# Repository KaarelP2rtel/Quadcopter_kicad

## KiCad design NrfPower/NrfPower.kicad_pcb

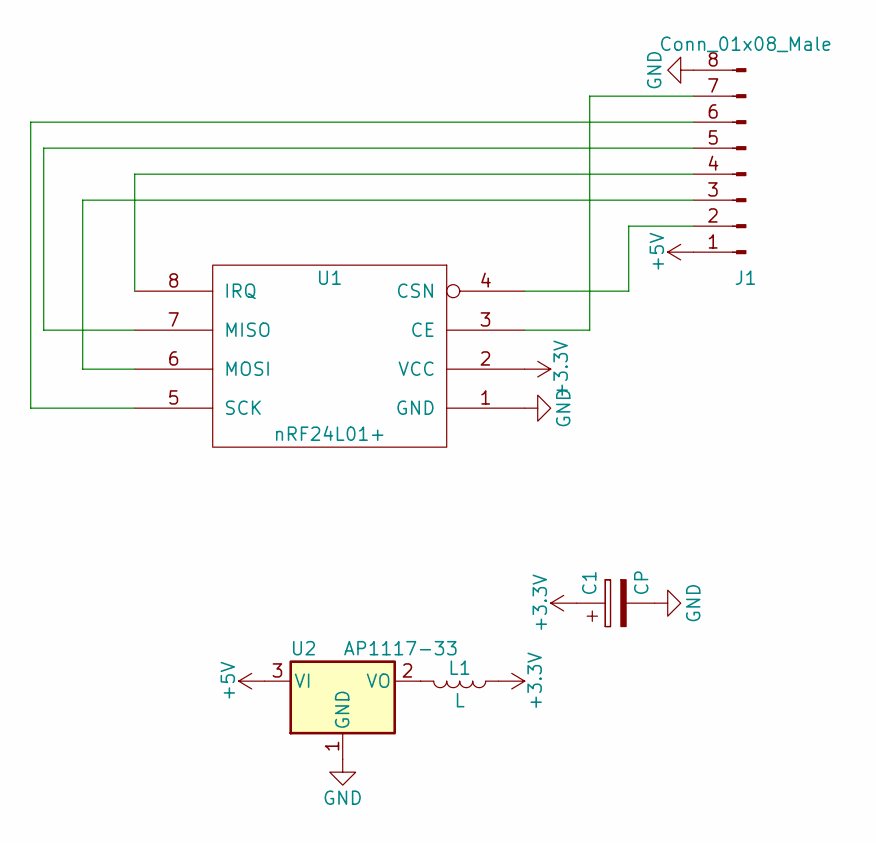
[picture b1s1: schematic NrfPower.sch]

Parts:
C1: CP; CP_Radial_D8.0mm_P5.00mm
J1: Conn_01x08_Male; Pin_Header_Straight_1x08_Pitch2.54mm
L1: L; L_Radial_D9.5mm_P5.00mm_Fastron_07HVP
U1: nRF24L01+; Pin_Header_Straight_2x04_Pitch2.54mm
U2: AP1117-33; SOT-223-3_TabPin2

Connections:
+3V3: C1.1, L1.1, U1.2 (VCC)
+5V: J1.1, U2.3 (VI)
GND: C1.2, J1.8, U1.1 (GND), U2.1 (GND)
unnamed: J1.2, U1.4 (CSN)
unnamed: J1.3, U1.6 (MOSI)
unnamed: J1.4, U1.8 (IRQ)
unnamed: J1.5, U1.7 (MISO)
unnamed: J1.6, U1.5 (SCK)
unnamed: J1.7, U1.3 (CE)
unnamed: L1.2, U2.2 (VO)

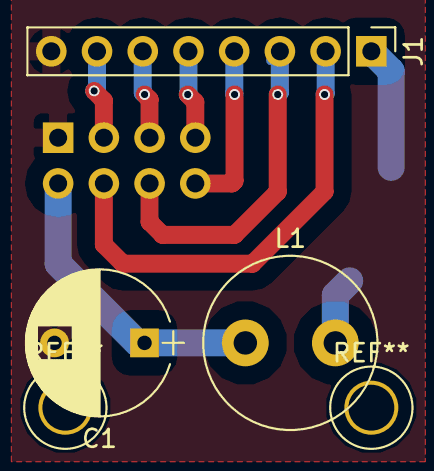
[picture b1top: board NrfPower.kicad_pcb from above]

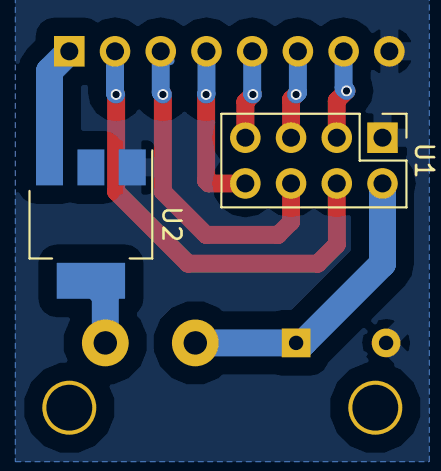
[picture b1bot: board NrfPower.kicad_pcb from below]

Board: 2 copper layers, 5 parts (2 on the bottom side), 10 nets.

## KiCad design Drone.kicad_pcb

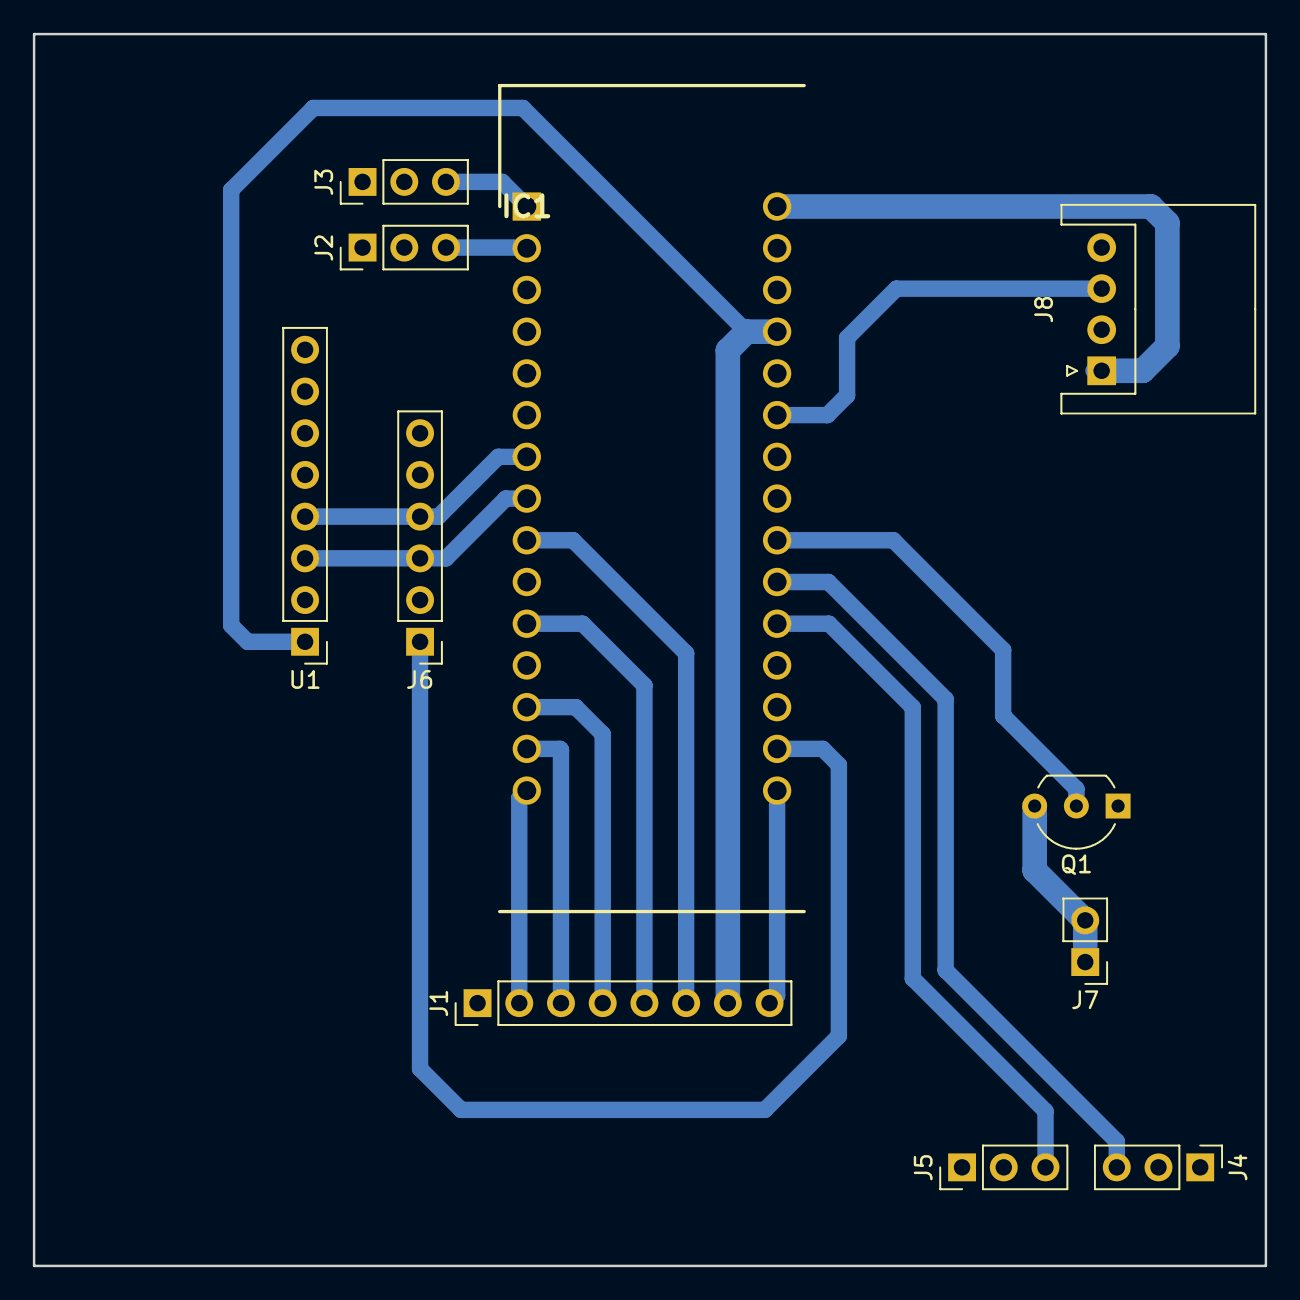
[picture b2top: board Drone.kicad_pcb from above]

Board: 2 copper layers, 75.0 x 75.0 mm, 11 parts (0 on the bottom side), 19 nets.

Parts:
IC1: NUCLEO-F303K8; DIPS1524W66P254L5029H1500Q30N
J1: Conn_01x08_Male; Socket_Strip_Straight_1x08_Pitch2.54mm
J2, J3, J4, J5: Conn_01x03_Male; Pin_Header_Straight_1x03_Pitch2.54mm
J6: Conn_01x06; Socket_Strip_Straight_1x06_Pitch2.54mm
J7: Conn_01x02; Pin_Header_Straight_1x02_Pitch2.54mm
J8: Conn_01x04; JST_XH_S04B-XH-A_04x2.50mm_Angled
Q1: 2N7000; TO-92_Inline_Wide
U1: GY-521; Pin_Header_Straight_1x08_Pitch2.54mm

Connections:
+3V3: IC1.17, J6.1
+5V: IC1.27, J1.7, U1.1
GND: IC1.4, IC1.29, J1.1, J2.1, J3.1, J4.1, J5.1, J6.2, J8.4, Q1.1, U1.2
unnamed: IC1.1, J3.3
unnamed: IC1.2, J2.3
unnamed: IC1.7, J6.4, U1.4
unnamed: IC1.8, J6.3, U1.3
unnamed: IC1.9, J1.6
unnamed: IC1.11, J1.5
unnamed: IC1.13, J1.4
unnamed: IC1.14, J1.3
unnamed: IC1.15, J1.2
unnamed: IC1.16, J1.8
unnamed: IC1.20, J5.3
unnamed: IC1.21, J4.3
unnamed: IC1.22, Q1.2
unnamed: IC1.25, J8.3
unnamed: J7.1, J7.2, Q1.3
VCC: IC1.30, J8.1

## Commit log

2018-10-29 Added project to source control
